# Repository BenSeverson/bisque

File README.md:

<p align="center">
  <picture>
    <source media="(prefers-color-scheme: dark)" srcset="docs/logo-banner-dark.svg" />
    
  </picture>
</p>

<p align="center">

</p>

<p align="center">
  <a href="https://benseverson.github.io/bisque/"><b>▶ Try the live web UI demo</b></a> — interactive, no hardware required
</p>

## Features

**Temperature Control**
- PID controller with auto-tuning (Ziegler-Nichols relay method)
- 1-second control loop with time-proportional SSR output
- Thermocouple calibration offset

**Firing Profiles**
- Up to 20 custom profiles with 16 segments each (ramp rate, target temp, hold time)
- Orton cone firing (cones 022-13) with slow, medium, and fast heating speeds
- Delayed start

**Safety**
- Over-temperature protection (hardware max 1400 C, user-configurable limit)
- Thermocouple fault detection (open circuit, short to GND/VCC)
- Rate-of-rise monitoring (detects runaway >2x programmed rate)
- Not-rising detection (alerts if <10 C rise in 15 min)
- Emergency stop with immediate SSR cutoff

**Web Dashboard**
- Real-time temperature chart with profile overlay (React + Recharts)
- Profile builder with cone fire mode
- Firing history with CSV trace export and cost estimation
- Settings: calibration, safety limits, webhooks, API token

**iOS App**
- Full remote control (SwiftUI)
- Finds the kiln on your Wi-Fi automatically (Bonjour), no IP address to type
- Dynamic Island live activities during firing
- Local notifications for firing complete/error

**LCD Display**
- 4.0" TFT (480x320) with LVGL, adaptive single-screen dashboard (idle/active/paused/complete/error)
- 5-way nav switch (up/down/select/left/right), SELECT-driven modals for profile pick and firing control

**Connectivity**
- Wi-Fi with mDNS (`bisque.local`)
- REST API with optional bearer token auth
- WebSocket for real-time streaming
- Webhook notifications (firing complete/error)

## Screenshots

**Web Dashboard** (React)

**LCD Display** (LVGL on 4.0" TFT)

**iOS App** (SwiftUI)

## Hardware

The controller is a single board in [`hardware/kicad/`](hardware/kicad/) — a full KiCad project (schematic + routed **4-layer** board, 100 × 100 mm). Its GPIO map is [`docs/pin-assignments.md`](docs/pin-assignments.md).

It integrates the ESP32-S3-WROOM-1U module (external U.FL antenna), two MAX31856 thermocouple front-ends, two SSR drive channels behind a hardware watchdog, an ADE7953 current-sense front-end, a ULN2003 auxiliary output bank, three protected dry-contact inputs, USB-C flashing, status LED, and alarm buzzer — with screw terminals for the field wiring and keyed connectors for the display and nav-switch looms. Gerbers, drill files, and an assembly BOM/CPL are committed and ready to upload to a board house.

See [`hardware/kicad/README.md`](hardware/kicad/README.md) for the full BOM, fabrication notes, and the regeneration workflow. GPIO assignments mirror the firmware's `Kconfig` defaults, so stock firmware runs unmodified.

[`hardware/enclosure/`](hardware/enclosure/README.md) documents a complete enclosure build around an off-the-shelf wall-mount steel box — layout, SSR thermal sizing, mains/SELV segregation, and a printable 1:1 drill template for the door.

> **Safety warning:** Kilns operate at dangerous temperatures and voltages. Ensure all high-voltage wiring is performed by a qualified electrician. Use appropriate safety equipment and never leave a firing kiln unattended.

## Getting Started

### Prerequisites

- [ESP-IDF v6.1](https://docs.espressif.com/projects/esp-idf/en/v6.1/esp32s3/get-started/)
- Node.js 18+
- [XcodeGen](https://github.com/yonaskolb/XcodeGen) (for iOS development)

### Dev Container (recommended)

The fastest way to a reproducible toolchain is the VS Code dev container — it
pins the exact ESP-IDF v6.1 image CI uses plus Node 24, the static-analysis
tools, and the Claude Code CLI. Open the repo in VS Code and run **Dev
Containers: Reopen in Container**. Everything below (firmware build, web UI,
`make ci`) then works in the container terminal; only flashing needs a bench.
See [docs/devcontainer.md](docs/devcontainer.md).

### Firmware

```bash
# Build web UI assets first
cd web_ui && npm install && npm run build && cd ..

# Gzip assets for SPIFFS
gzip -k -9 spiffs_data/www/assets/*.js spiffs_data/www/assets/*.css

# Build and flash firmware
source ~/.espressif/v6.1/esp-idf/export.sh
idf.py build
idf.py flash monitor
```

### Web UI Development

```bash
cd web_ui
npm install
npm run dev    # Starts dev server with mock kiln simulator
```

### iOS App

```bash
# Generate Xcode project
cd ios/Bisque
xcodegen generate
open Bisque.xcodeproj
```

For simulator testing, start the mock server first:

```bash
cd web_ui && npm run mock-server   # HTTP + WebSocket on localhost:8080
```

In the iOS simulator, tap "Use Mock Server" on the connection screen.

<details>
<summary><strong>Simulator / Mock Server</strong></summary>

A mock kiln server simulates the full API (status, profiles, firing, settings, history, autotune, diagnostics) with realistic temperature physics so you can develop and test without hardware.

### Web UI development

The mock server runs automatically as a Vite plugin when you start the web UI dev server:

```bash
cd web_ui
npm run dev
```

The mock is enabled by default. To disable it and proxy to a real kiln instead:

```bash
VITE_MOCK=false npm run dev
```

Control simulation speed with `VITE_MOCK_SPEED` (default `60` = 60x real-time):

```bash
VITE_MOCK_SPEED=120 npm run dev
```

### iOS app development

A standalone mock server is available for testing the iOS app in the Xcode simulator:

```bash
cd web_ui
npm run mock-server
```

This starts an HTTP + WebSocket server on `localhost:8080`. To change the port or simulation speed:

```bash
MOCK_PORT=9000 MOCK_SPEED=120 npm run mock-server
```

### LCD Simulator

A standalone SDL2-based simulator renders the LVGL display UI on your desktop:

```bash
cd simulator
cmake -B build && cmake --build build
./build/bisque_sim
```

Requires SDL2 (`brew install sdl2` on macOS).

</details>

## Architecture

```
main/                 App entry point, FreeRTOS task creation
components/
  app_config/         Pin definitions, hardware constants
  thermocouple/       MAX31856 SPI driver (2 channels)
  pid_control/        PID controller + Ziegler-Nichols auto-tune
  firing_engine/      Multi-segment firing state machine
  safety/             Watchdog, over-temp, fault detection
  cone_table/         Orton cone temperature lookup (022-13)
  history/            Firing history + temperature traces (NVS)
  display/            ST7796S LCD + LVGL UI (adaptive dashboard)
  web_server/         REST API + WebSocket server
  wifi_manager/       Wi-Fi STA/AP + mDNS
web_ui/               React/TypeScript web dashboard
ios/Bisque/           SwiftUI iOS app
simulator/            LVGL SDL2 desktop simulator
tests/host/           Pure-logic + accelerated firing unit tests (CMake/Unity)
docs/                 Wiring diagrams, screenshots, bench smoke test
```

## Testing

CI runs five automated test layers on every PR — pure-logic unit tests
and accelerated firing scenarios (`tests/host/`), a UI screenshot
regression suite (`simulator/ --diff`), web UI unit tests, and a
cross-language API contract test that validates firmware JSON output
against the frontend's zod schemas.

Before tagging a release, run the [bench smoke test](docs/bench-smoke-test.md) — a 3-8 minute hardware
run that verifies the parts CI can't touch: real SSR clicks, real
thermocouple readings, history persistence across reboot.

## Network security

**Bisque assumes the network it sits on is trusted.** It is a LAN-only
device: the HTTP API and the WebSocket telemetry feed are plain `http://`
and `ws://`, with no TLS. Anyone who can see traffic on the same Wi-Fi can
read the API token and every command sent with it.

The optional API token (Settings → API Token) is therefore a lock on the
front door, not protection against a hostile network. It stops a
housemate's laptop or a curious guest from starting a firing; it does not
stop someone who is already capturing your Wi-Fi traffic. Concretely:

- The token is sent as an `Authorization: Bearer` header on every REST
  request and compared in constant time on the device.
- The WebSocket telemetry feed (`/api/v1/ws`) is authenticated by the same
  check as the REST API. Browsers cannot set headers on a WebSocket
  handshake, so the web UI presents the token as a `?token=` query
  parameter instead — which means that on this one route the credential does
  reach anywhere the URL does, including proxy logs and browser history. The
  iOS app uses `URLSession`, which can set the header, and does. Dropping the
  query parameter would lock every browser out of live telemetry, so it is a
  deliberate trade rather than an oversight.
- Firmware updates are fetched over HTTPS with certificate validation
  against the bundled root store, and the downloaded image is checked
  against the SHA-256 in the release manifest. So an OTA is not exposed by
  the local network being readable — its trust rests on GitHub's TLS, not on
  your LAN.

If that trust assumption does not hold for your network, put the kiln on an
isolated VLAN or guest SSID rather than relying on the token. TLS on-device
with certificate pinning in the clients has been considered and is tracked
in [#149](https://github.com/BenSeverson/bisque/issues/149); it is a
significant amount of firmware and app complexity for a home LAN, and has
not been implemented.

**Never expose a kiln controller directly to the internet.** No port
forwarding, no DMZ. This is a device that applies mains power to a heating
element in an unattended room.

## Releases

Firmware is distributed as [GitHub Releases](https://github.com/BenSeverson/bisque/releases),
each with a full ESP32-S3 flash kit and Sigstore build-provenance
attestations. See [RELEASING.md](RELEASING.md) for the versioning scheme and
the procedure for cutting a release.

## License

[MIT](LICENSE)

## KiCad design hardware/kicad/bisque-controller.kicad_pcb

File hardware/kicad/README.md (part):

# Bisque Kiln Controller — KiCad PCB

The controller board. This is **rev B**, a respin of the original prototype
rather than a variant — it replaced the thermocouple front-end with an
incompatible part, added a second SSR zone and a digital current-sense chip,
moved most GPIOs, and swapped the module variant.
4-layer, 100 × 100 mm, built for **JLCPCB assembly**: 0805 passives,
QFN/TSSOP/SOIC/SOT ICs, SMD tact switches and the ESP32-S3-WROOM-1U module's
castellated pads all go down the SMT line, and JLCPCB hand-solders the twelve
through-hole parts (terminals, wafers, buzzer) on the same order — see
"Fabrication & assembly" below for why that is cheaper than fitting them
yourself. The design record for
this respin, including the routing escalation that forced the layer count,
is `docs/superpowers/specs/2026-08-10-pcb-rev-b-hardware-design.md`; the
fab-readiness sign-off is `FAB-READINESS-REVIEW-REVB.md`.

Built and validated with **real KiCad** (10.0.5, pcbnew Python API +
kicad-cli): footprints come from KiCad's installed libraries, ground/power
plane pours are filled and checked by `kicad-cli pcb drc --refill-zones` —
**zero errors, zero unconnected, zero warnings**
(`bisque-controller-drc.rpt`) — and the schematic passes a netlist round-trip
check (KiCad's exported netlist diffed against the design's connectivity
table — 92 nets, 0 mismatches). The 3D renders in `3d/` are raytraced by
`kicad-cli pcb render` with the official component models.

| File | What it is |
|---|---|
| `bisque-controller.kicad_pro` | Project. Hand-maintained **except** two blocks, both derived and both written *after* the board is saved because `pcbnew.SaveBoard()` blanks them: `schematic.top_level_sheets` (`project_sync.py::sync_project()`) and `net_settings` (`gen_pcb.py::sync_netclasses()`, from `ROUTE_ORDER`) — see below |
| `bisque-controller.kicad_sch` | Root of the hierarchical schematic: a sheet symbol per functional area (`sheets/power`, `mcu`, `kiln`, `io`, `ct`) plus the notes block and the mechanical parts (mounting holes H1–H4, fiducials FID1–FID3), wired as a block diagram: each sheet symbol carries a pin per net that crosses sheets. Within a sheet: one hierarchical label per crossing net, local labels for everything else, real power ports for rails; no global labels. Hand-owned; `make pcb-netlist` exports its connectivity. |
| `bisque-controller.kicad_pcb` | Board: placed, fully routed, 4 layers (F.Cu/B.Cu signals, In1.Cu GND plane, In2.Cu +3V3 plane), on JLCPCB's `JLC04161H-7628` 1.6 mm stack-up — see "The physical stack-up" |
| `bisque-controller.kicad_dru` | JLCPCB's standard 4-layer process as KiCad custom rules — **not generated**, and not a statement of design intent: every limit in it is JLC's *absolute minimum*, so a violation means something slipped off the design's own floor (0.3 mm track, 0.2 mm clearance, 0.6/0.3 vias, all from `net_settings`) far enough to hit the fab's. KiCad reads it by project name, so it survives regeneration untouched and the existing `kicad-cli pcb drc` pass picks it up for free — see "Fabrication & assembly at JLCPCB" |
| `3d/board-3d-*.png` | Raytraced renders, kicad-cli — straight orthographic **top** and **bottom** only. The angled iso/front views were dropped: they look better than they read, and these images get used to check placement and silk, not to advertise |
| `bisque-controller-drc.rpt` | KiCad DRC report, now including the `.kicad_dru` rules above (0 errors, 0 unconnected, 0 warnings — the 109 silkscreen warnings went with the silk packer, see "Regenerating the files") |
| `gerbers/` | Fabrication outputs (kicad-cli: F.Cu, B.Cu, **In1.Cu, In2.Cu**, paste/silk/mask, Edge.Cuts, Excellon drill + job file) |
| `pdf/` | Schematic and board PDFs (kicad-cli) |
| `jlcpcb/` | The complete JLCPCB upload: `gerbers.zip` for fabrication, BOM + CPL for assembly, plus the shopping list for the parts you could hand-solder instead, and `mouser-order.csv` for the mating connectors |
| `generator/` | Scripts that build everything from one connectivity table |

## Opening it

Open `bisque-controller.kicad_pro` in KiCad 10 or newer (the board file
format and pcbnew API this generator uses require it — see "Regenerating the
files"). Zones ship **filled** (KiCad's own filler) and the board already
passes KiCad DRC; re-run it after any edit. The schematic embeds its
symbols; the board references the standard KiCad footprint libraries (and
was generated from them), plus the four vendored models in `3dmodels/`.

**Opening the project used to dirty it.** KiCad records the root sheet under
`schematic.top_level_sheets` in the `.kicad_pro` and writes that block itself
the first time anything touches the project — and what it writes depends on
who wrote it. The GUI knows the schematic's real root uuid; `kicad-cli pcb`
fills all-zeros, because the PCB tooling never loads a schematic and has no
uuid to record. So the file grew an unexplained diff after a regen and could
flip between two values depending on which tool ran last.

`project_sync.py::sync_project()` (used by `sync_board.py`) now derives the entry from the same `ROOT`
constant the schematic's own `(uuid ...)` comes from, and runs on every
`pcb-sync`. Whoever opens the project next finds it already
correct and leaves it alone — kicad-cli only ever *adds* the block when it is
missing and preserves a populated one, which is what makes deriving it
sufficient rather than a tug-of-war. The rewrite is a whole-file json
round-trip, safe because KiCad emits plain 2-space-indented JSON that
re-dumps byte for byte; do not replace it with a hand-rolled text patch.

## What's on the board

- **U1 — ESP32-S3-WROOM-1U-N16R2** module (16 MB flash / 2 MB **quad**
  PSRAM — matches `sdkconfig.defaults`' `CONFIG_SPIRAM_MODE_QUAD` + the
  16 MB OTA partition table), at the top edge. The **1U** variant carries a
  **U.FL connector for an external antenna** rather than the standard
  WROOM-1's on-package PCB antenna: a kiln controller mounts on or near a
  large grounded steel enclosure, which makes a PCB antenna close to
  non-functional, and the 1U's antenna can be placed on a pigtail somewhere
  that actually radiates. It also reclaims the ~330 mm² antenna keep-out
  band the WROOM-1 footprint would require — freed for parts and ground
  pour on a board that turned out to need every square millimeter (see
  "Density and the 4-layer stack-up" below). **The U.FL pigtail (U.FL → SMA
  bulkhead) and the 2.4 GHz antenna are accessories, not BOM lines** — buy
  them separately (see the hand-solder/shopping-list note below) and drill
  an SMA bulkhead hole in the enclosure. U.FL is rated for ~30 mating
  cycles, so treat the connection as assemble-once, not a field-serviceable
  connector.

  **Certification caveat.** Espressif's modular certification for the
  WROOM-1U is granted against specific antenna types and gains. Fitting a
  non-approved (e.g. high-gain) antenna steps outside that approval — see
  `CERT-001` in `FAB-READINESS-REVIEW-REVB.md`. Use an antenna within the
  certified list unless you're prepared to re-certify.

- **Power**: 24 V DC in on screw terminal **J2** (top-left) *or* USB-C.
  The 24 V side runs J2 → F1 (750 mA/33 V resettable fuse) → D8 (SMAJ30A TVS)
  → **Q8** (AO3401A P-FET, reverse polarity) → **U11**, an XL1509-5.0 buck in
  the south-east corner that makes `BUCK_5V`; **U12** (TPS2116) then selects
  between `BUCK_5V` and USB VBUS to make `+5V`, and a **TLV1117LV33**
  (U2, SOT-223) drops that to 3V3.
  Regulating rather than dropping is the point: +5V used to be literally the
  input minus a Schottky, so every diode drop and every turn of the
  installer's trim pot landed on the WS2812B threshold, the SSR drive and the
  relay coil at once. Both of the board's remaining series diodes are now
  gone with it — the reverse-polarity SS34 is Q8 (~39 mV instead of ~0.4 V,
  which matters because `VIN_P` feeds both 24 V SSR terminals as well as the
  buck) and the USB ORing SS34 is U12 (~40 mΩ).

  **U12 runs in priority mode, not highest-voltage-wins, and that is the
  whole reason it is a mux and not an ideal diode.** A 5.25 V USB host is
  higher than a 5.0 V buck, so a plain ORing part would let a laptop source
  the relay bank and both SSR terminals; the diode used to prevent that for
  free by dropping. MODE ties to VIN1 and R63/R64 divide `BUCK_5V` into PR1
  with a 4.0 V threshold, so the buck wins whenever it is up. U12 also
  blocks USB back-feeding the unpowered buck, which closes fab-review
  finding **C1** (5 V on U11's FB and switch pins during every USB-only
  flashing session). Its ST pin is left unconnected on purpose — see
  `DESIGN-NOTES.md` at U12 for why that GPIO is not worth the route.

  `BUCK_5V` and `+5V` are deliberately separate nets: C44/**C46** are the
  buck's compensation (C46 is the electrolytic supplying the ESR zero — since
  2026-10-28 a Panasonic FK with its 0.36 Ω *specified* at 100 kHz, beside one
  22 µF ceramic rather than two; `DESIGN-NOTES.md` at C46 and C44) and
  belong on the buck's side of the mux, not the load's. The input pair C41/C42
  is chosen on Samsung's bias curve: 1210 X7R 4.7 µF holding 3.1 µF each at
  24 V, where the 1206 10 µF they replace held 1.35 µF. The 5 V rail is rated
  1.0 A at 50 °C in-box ambient (`DESIGN-NOTES.md` at C41, "LOAD BUDGET");
  the regulator's 2 A headline is not a rating of this board.
  Power LED (green) on 3V3. The display (below) draws from +5V directly, not
  through U2 — its backlight and panel logic were the dominant unmodeled load
  on the LDO, and moving them off keeps U2's junction temperature comfortably
  under its 125°C limit even at a hot enclosure ambient. The +3V3 rail also
  now lives on its own **inner plane** (In2.Cu) rather than a surface pour —
  see the stack-up note below.
- **Thermocouples ×2**: **MAX31856MUD+** (U3 channel 1 / U5 channel 2,
  TSSOP-14), K-type on screw terminals **J3** (channel 1) / **J8** (channel
  2), each with its datasheet-specified differential + common-mode input
  filter, sharing the SPI bus (MISO + its own CS: `TC1_CS` / `TC2_CS`). This
  replaces rev A's single MAX31855KASA+ entirely — the two parts are not
  pin-compatible, and no attempt was made to support both on one board.

  **Ungrounded-junction thermocouple probes are required.** Both MAX31856s
  reference their T− input to board ground. Two grounded-junction probes
  sharing one kiln chamber would form a ground loop through the kiln body
  itself; use ungrounded-junction (isolated-tip) K-type probes on both
  channels. This is a documentation obligation, not something the board
  enforces electrically.
- **SSR drive ×2, 24 V opto-driven high-side P-FET, ground-referenced (rev
  B.4)**: screw terminals **J4** (zone 1) / **J9** (zone 2), each
  **pin 1 = the switched +** (`SSR1_OUT` / `SSR2_OUT`, silk `OUT`) and
  **pin 2 = board `GND`**. Per channel: GPIO → 220 Ω → the LED of a TLP291
  (**U8** zone 1, **U9** zone 2) → GND; the opto's transistor pulls the gate
  of an **LP2309LT1G** (**Q5** / **Q6**, 60 V P-channel) down through
  **10 kΩ** (R69/R70), an **8.2 V zener** (D13/D14) gate-to-source sets the
  drive from the rail, and **10 kΩ** (R7/R20) gate-to-source holds it off.
  Both sources hang off **`SSR_24V`**, which is `VIN_P` through **Q9**, a
  third LP2309LT1G that is the watchdog's cutoff (see below). A green
  indicator LED (LED3/LED4, amber before the 2026-11-07 BOM-line merge) + 10 kΩ sits across each terminal pair, so it lights only
  when the channel is actually conducting. **D9**/**D10** freewheel each
  terminal for inductive loads. The board supplies the SSR control loop.
  (The SSRs themselves and all mains wiring stay outside this board.)
  Because the `−` pin is ground, an SSR lead that chafes onto the earthed
  enclosure is the wiring diagram, not a fault — the 2026-10-05 review's
  item 3, which B.2's switched-return topology could not cover. Rev B.2/B.3
  boards had pin 1 always live (silk `24V`) and switched the return; the
  pin order is unchanged, so a loom built to that silk still lands right.

  **Current budget, and it is a limit rather than a note.** The two channels
  share what is left of F1's *derated* hold current after the buck: **280 mA
  at the board's 50 °C in-box rating, 180 mA at 60 °C** (derived at F1 in
  `DESIGN-NOTES.md`, 2026-10-29, from the PPTC's derating table, the
  HDR-15-24's own derating and U11 at its 1.0 A ceiling). Two SSR inputs
  plus their indicators is ~40 mA and fits at any ambient. One 24 V coil
  beside an SSR: ≤ 260 mA (6.2 W) at 50 °C, ≤ 160 mA at 60 °C — a 5.4 W
  TeSys-D-class coil fits at 50 °C and not at 60. Two coils: ≤ 140 mA each
  at 50 °C, ≤ 90 mA each at 60 °C. The "~400 mA" quoted before was the 25 °C
  figure. F1 is not enlarged to buy more: under the in-box supply the
  supply's 0.63 A is the next limit anyway, and a 1.1 A PPTC's 2.2 A trip
  would put the clamped fault rail at 39.9 V against U11's 40 V.

  **The optocouplers are containment, not isolation, and that distinction is
  load-bearing.** Rev B opto-*isolated* both channels — dry-contact terminals,
  a four-layer pour keepout across the opto row, `SJ3`/`SJ4` to tie each
  collector to board +5 V, and `check_isolation.py` — and that was **reversed**
  before fab, because an optocoupler only isolates if the SSR control loop is
  powered from a supply that is *not this board*, and this board's is.
  **That reasoning still stands and is not being overturned.** These terminals
  are still board-powered, both sides still share `GND`, and there is still no
  pour keepout, no router keepout, no rule area and no `check_isolation.py`.
  Do not re-add any of them; read commit `93a31d7` first.

  What changed is the failure the parts are bought for. At 5 V, a channel
  MOSFET failing gate-to-drain put 5 V through 100 Ω into a GPIO and the
  ESP32's clamp survived it. At 24 V the same single failure puts ~240 mA into
  that clamp and takes the module with it. The opto removes the conductor: the
  only thing the MCU touches is an LED. It is also not more parts than the
  alternative — a gate-to-GND zener contains the same fault for the same one
  part per channel, but contains it *by conducting*, so it has to survive the
  fault to work and fails open silently.

  **The opto is a TLP291 in SOP-4, not the LTV-817S this started as, and the
  reason is geometry.** The SMD-DIP4 body is 12.04 mm across its courtyard;
  the corridor between `J4`/`J9` and the rest of the block is ~5.5 mm and has
  to carry both these parts and the four per-terminal legends (`OUT`/`GND`,
  each locked to its own screw's y and free only in x). A 12 mm opto leaves
  those legends nowhere to go, and they print on the terminal body — three
  `check_silk` failures that no amount of re-spacing fixes, because the
  corridor is simply too narrow. At 8.50 × 3.10 mm it opens to ~6.7 mm.
  It costs one Extended feeder where the LTV-817S was Basic, and buys 80 V
  `V_CEO` against 35 V, which is free margin on a 24 V board.

  The 220 Ω is sized against the ESP32's **guaranteed** `V_OH`
  (0.8 × VDD = 2.64 V), not against 3.3 V: the opto's CTR bin is only
  specified at `I_F` = 5 mA and falls off steeply below it, and 330 Ω at that
  corner gives 4.7 mA. 220 Ω gives 7.0 mA there, 5.6 mA with `V_F` also at
  its maximum, and 10.0 mA typical — half the ESP32's recommended source
  current.

  The gate drive comes from a **zener, not from the opto's CTR**, and that is
  deliberate: with the opto saturated the R69/R7 pair alone would put half
  the rail across the gate (11.9 V at 24 V, 18.8 V in a clamped 38 V fault,
  24 V on the 48 V transient), so D13/D14 clamp `V_SG` to 8.2 V from
  ~17 V upwards — the whole 21.6–29 V trim range and the fault alike. The
  opto then sinks (`V_rail` − 8.5 V)/10 kΩ: 1.55 mA at 24 V, 2.95 mA in the
  fault, against the ≥ 5.6 mA a GB-rank TLP291 passes at the worst-case LED
  current. Off, the opto's 50 µA of 85 °C dark current across R7 is 0.5 V
  against the LP2309LT1G's 1 V minimum threshold. Rev B.2 got the same
  "from a rail, not a ratio" property by hanging the opto collectors on the
  5 V `SSR_EN`; that rail now has nothing to do with the channels directly.

  **Hardware watchdog (`SJ2`, "WDT DEFEAT").** `SSR_EN` — since rev B.2 a
  +5 V **gate-drive** rail rather than the terminal supply — is supplied by
  Q4, a P-channel high-side MOSFET (AO3401A) whose gate node `SSR_PG` is held
  down by Q3, itself held on by **U10**, an SN74LVC1G123 retriggerable
  monostable driven from `WDT_KICK`; R47 (100 kΩ) pulls `SSR_PG` up
  as the fail-safe. `SSR_EN` enhances **Q7** (CJ2310), which pulls the gate
  of **Q9** — the 24 V high-side cutoff between `VIN_P` and `SSR_24V` — down
  through R71 (10 kΩ); D12 clamps Q9's `V_SG` to 8.2 V and **R22** (100 kΩ,
  gate to source) holds Q9 off whenever Q7 is not pulling. When the window
  expires `SSR_EN` falls, R18 (10 kΩ) takes Q7's gate down, R22 takes Q9's
  gate to its source and `SSR_24V` is dead: both terminals are off whatever
  the channel switches are doing, a failed-short channel included. **R18**
  is what makes that work — `SSR_EN` is Q4's *drain*, so with Q4 off nothing
  would define it and Q7's gate would float, the same fail-dangerous bug R49
  exists to fix one node upstream.

  **Q9 is the high-side cutoff B.2 rejected, and the reason it was rejected
  is gone.** B.2 kept the watchdog in the shared *return* (Q7 as the switch)
  because no fee-free 60 V P-channel part existed at JLCPCB; the only one was
  a 50 V/130 mA BSS84 that capped the terminals below their own budget. On
  Standard PCBA — which U1 and C46 force — every line pays the same $1.53,
  and the LP2309LT1G (60 V, 1.9 A, LCSC C383253) is the part the objection
  said did not exist. The return-side watchdog also could not touch an SSR
  `−` lead that found ground (review A1 / item 3), and it let a failed-short
  channel put −23.7 V on the healthy channel's gate through R22 (item 11);
  with the switches on the + side and the cutoff in series with the rail,
  both of those go away. Q7 survives as the level shift because its gate is
  on a 5 V rail where the CJ2310 is specified, the argument B.2 made for it.

  Every **rising edge** on `WDT_KICK` restarts U10's window, so `Q` stays high
  only while firmware keeps kicking; a pin wedged at either level delivers no
  edge and expires the window exactly like a pin that stopped, which is the
  whole point. R46 (1 MΩ) and C38 ∥ C49 (2 × 1 µF X7R) set the window to
  **1.3–3.1 s** worst-case over −40…125 °C (2.0–2.2 s nominal), every term of
  that bound a datasheet or purchase-tolerance figure. Firmware kicks at 5 Hz
  from the existing 100 ms SSR timer, gated on `safety_task`'s heartbeat
  (`components/safety/wdt_kick.h`) — 6.4× margin at the minimum window. R48
  (100 kΩ) holds `B` low whenever the MCU drives nothing, so a floating CMOS
  input cannot self-trigger the one-shot during boot ROM, flashing or reset.

  **This replaced a BAT54S diode charge pump, which did not work.** Solving its
  steady state exactly gives 0.63 V of gate drive at 5 Hz against Q3's 1.45 V
  threshold — and 0.84 V even in the typical corner, below the *typical* 1.0 V
  threshold. A faster kick (≥ 250 Hz) rescues the voltage but not the
  temperature behaviour: Schottky reverse leakage sits in the timing path and
  roughly doubles per 10 °C, so the budget for a transient firmware stall fell
  from 0.31 s at 25 °C to 0.11 s at 60 °C and vanished near 85 °C, next to a
  5 kW heat source. No choice of passives fixes a leak that *is* the timer;
  the fix was to stop building the timer out of one. Off-the-shelf watchdog
  supervisors (TPS3823, STWD100) were evaluated and rejected on output shape:
  they emit a fixed reset *pulse* per timeout, which would leave the heat rail
  energised 75–95 % of the time under dead firmware. They exist to reboot
  MCUs; gating a rail needs a level.

  On power-up, and on any board where nothing kicks `WDT_KICK`, `SSR_EN`
  collapses and **both SSR channels stay off regardless of what the firmware
  commands them to do.** The silkscreened `SJ2` solder jumper shorts `SSR_PG`
  to GND, holding Q4 on and restoring un-gated behaviour for bring-up and for
  any build without the firmware kick. **A board with neither `SJ2` fitted nor
  a working kick will not heat** — this is the single most likely rev B
  bring-up surprise, more likely to be mistaken for a bad SSR or a
  lid-interlock problem than correctly diagnosed as "nobody is kicking the dog
  yet." `TP12` probes the timing node, which is where a scope settles the real
  window in one measurement. The watchdog gates only the two SSR channels;
  vent, purge, the spare aux channel and the buzzer are unaffected, so a
  stalled controller can still open its vent.
- **Display**: 14-pin Molex KK-254 friction-lock header **J5** for a 4.0"
  ST7796S SPI module (LCDWIKI MSP4021, 480×320, resistive touch) — grown
  from rev A's 8-pin display-only header to carry the panel's full pin set:
  the original 8 signal pins, the panel's `SDO` (pin 9, left unwired in rev
  A because the firmware never read from the display), and the five touch
  lines (pins 10–14). `T_CLK`/`T_DIN`/`T_DO` are electrically the shared
  SPI2 bus through 33 Ω series damping resistors (R39/R41/R42 — the bus now
  multi-drops the LCD at 40 MHz plus two MAX31856s and the touch controller
  at lower clocks); only `T_CS` and `T_IRQ` cost new
  dedicated GPIOs. Since 2026-10-29 (PCB review item 5) SCLK and MOSI also
  leave the ESP32 through **R72/R73** (33 Ω, 0603) ahead of every branch —
  the pin-side stubs are `SPI_SCLK_U1`/`SPI_MOSI_U1` — and four 100 nF
  0603s (**C51–C54**) sit at the bus's layer transitions as +3V3-to-GND
  reference-transfer caps, with 29 GND stitch vias beside the rest (and 31 more, since 2026-10-30, beside the I2C and display/touch transitions). The
  honest coverage figures are in `DESIGN-NOTES.md` §C51; the 40 MHz
  waveforms are a bench check, not a proof. The XPT2046 touch controller itself lives on the display
  module, not this PCB. Since rev B.5 three SRV05-4 arrays (D19–D21) clamp
  all twelve J5 signal lines at the connector, and `LCD_RST`/`LCD_BL`, the
  two that had no series resistor, got 33 Ω (R79/R80). VCC runs from +5V rather than +3V3, per the
  module's own manual and reference wiring diagrams, with no level shifter
  needed on CS/RESET/DC/MOSI/SCK.
- **Nav switch**: 6-pin KK-254 friction-lock header **J6** for the
  panel-mounted 5-way switch (`UP DN LT RT OK GND`, active-low, ESP32
  internal pull-ups) — now on five contiguous module pads, moved from the
  split pins rev A used (routing simplification, see the hardware-design
  spec §3.1). Since rev B.5 an **ESDA6V1-5SC6** five-line array (D18)
  clamps the five switch lines to GND. There is no series resistor on
  them: ten more pad escapes did not fit beside J6 (`DESIGN-NOTES.md`
  §"Connector protection").
- **Aux header J7** (8-pin KK-254): `3V3 GND TX RX SDA SCL 3V3 GND` — UART0
  plus a 0.1" I2C tap (pins 5–8), alongside the Qwiic/STEMMA-QT connector
  **J14**. Rev A's `VENT`/`LID_SW`/`AUX_A`/`AUX_B` nets are gone from this
  header entirely: nothing on the board ever sourced `AUX_A`/`AUX_B` here
  (the real aux outputs are on J10, below), and the lid switch has its own
  terminal (J11). Since rev B.5 the 3V3 pins of J7 and J14 come from
  **U13**, an AP2331SA-7 current-limited switch (0.3–0.5 A short-circuit
  limit), so a shorted peripheral no longer drags the ESP32's rail down,
  and an SRV05-4 (D22) clamps TX, RX, SDA and SCL.
- **Aux output bank — J10 + J15** (two 2-pin terminals, side by side):
  **AUX_VP** (external coil rail) and `AUX1_OUT` (vent) on J10, `AUX2_OUT`
  and `AUX3_OUT` on J15, driven by a shared **ULN2003ADR** Darlington array (U6) with
  integrated freewheel diodes returning to `AUX_VP` — not the board's own
  +5V rail. A gas purge solenoid is realistically 12 V or 24 V DC; the
  ULN2003 is rated 50 V / 500 mA per channel, so `AUX_VP` is meant to be fed
  from an external coil supply. Solder jumper **`SJ1`** (open by default)
  ties `AUX_VP` to board +5V for anyone who only has plain 5V relays. Only
  channel 1 (vent) is driven by firmware today (`safety_update_vent()`);
  channels 2/3 are routed and declared in Kconfig (`KILN_PIN_AUX2`/`AUX3`)
  but undriven.
- **Protected inputs — J11 + J16** (two 2-pin terminals): `IN1`/`IN2` (lid,
  gas flow) on J11, `IN3` (spare) and GND on J16, for dry contacts to GND. Since rev B.5 each channel
  survives a 24 V wire landed on its terminal: a 10 kΩ pull-up to 3V3 and an
  **SMF30CA** bidirectional TVS (D15–D17, 30 V standoff, above the supply's
  29 V trim) sit on the terminal side, and the GPIO sees it through **100 kΩ**
  (R12/R26/R28) with 100 nF to ground, so a miswire puts 0.25 mA into the pin
  and 2.6 mA into the 3V3 rail instead of a short through a rail clamp.
  Firmware leaves the lid pin's internal pull-up off to match
  (`KILN_LID_SWITCH_EXTERNAL_PULLUP`, default on). `IN1` is the
  lid switch and defaults to enabled, matching this board; see
  `docs/pin-assignments.md` §1 for the fail-safe wiring requirement if no
  switch is fitted. `IN2` (gas flow) and `IN3` (spare) are routed but have
  no firmware consumer yet.
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
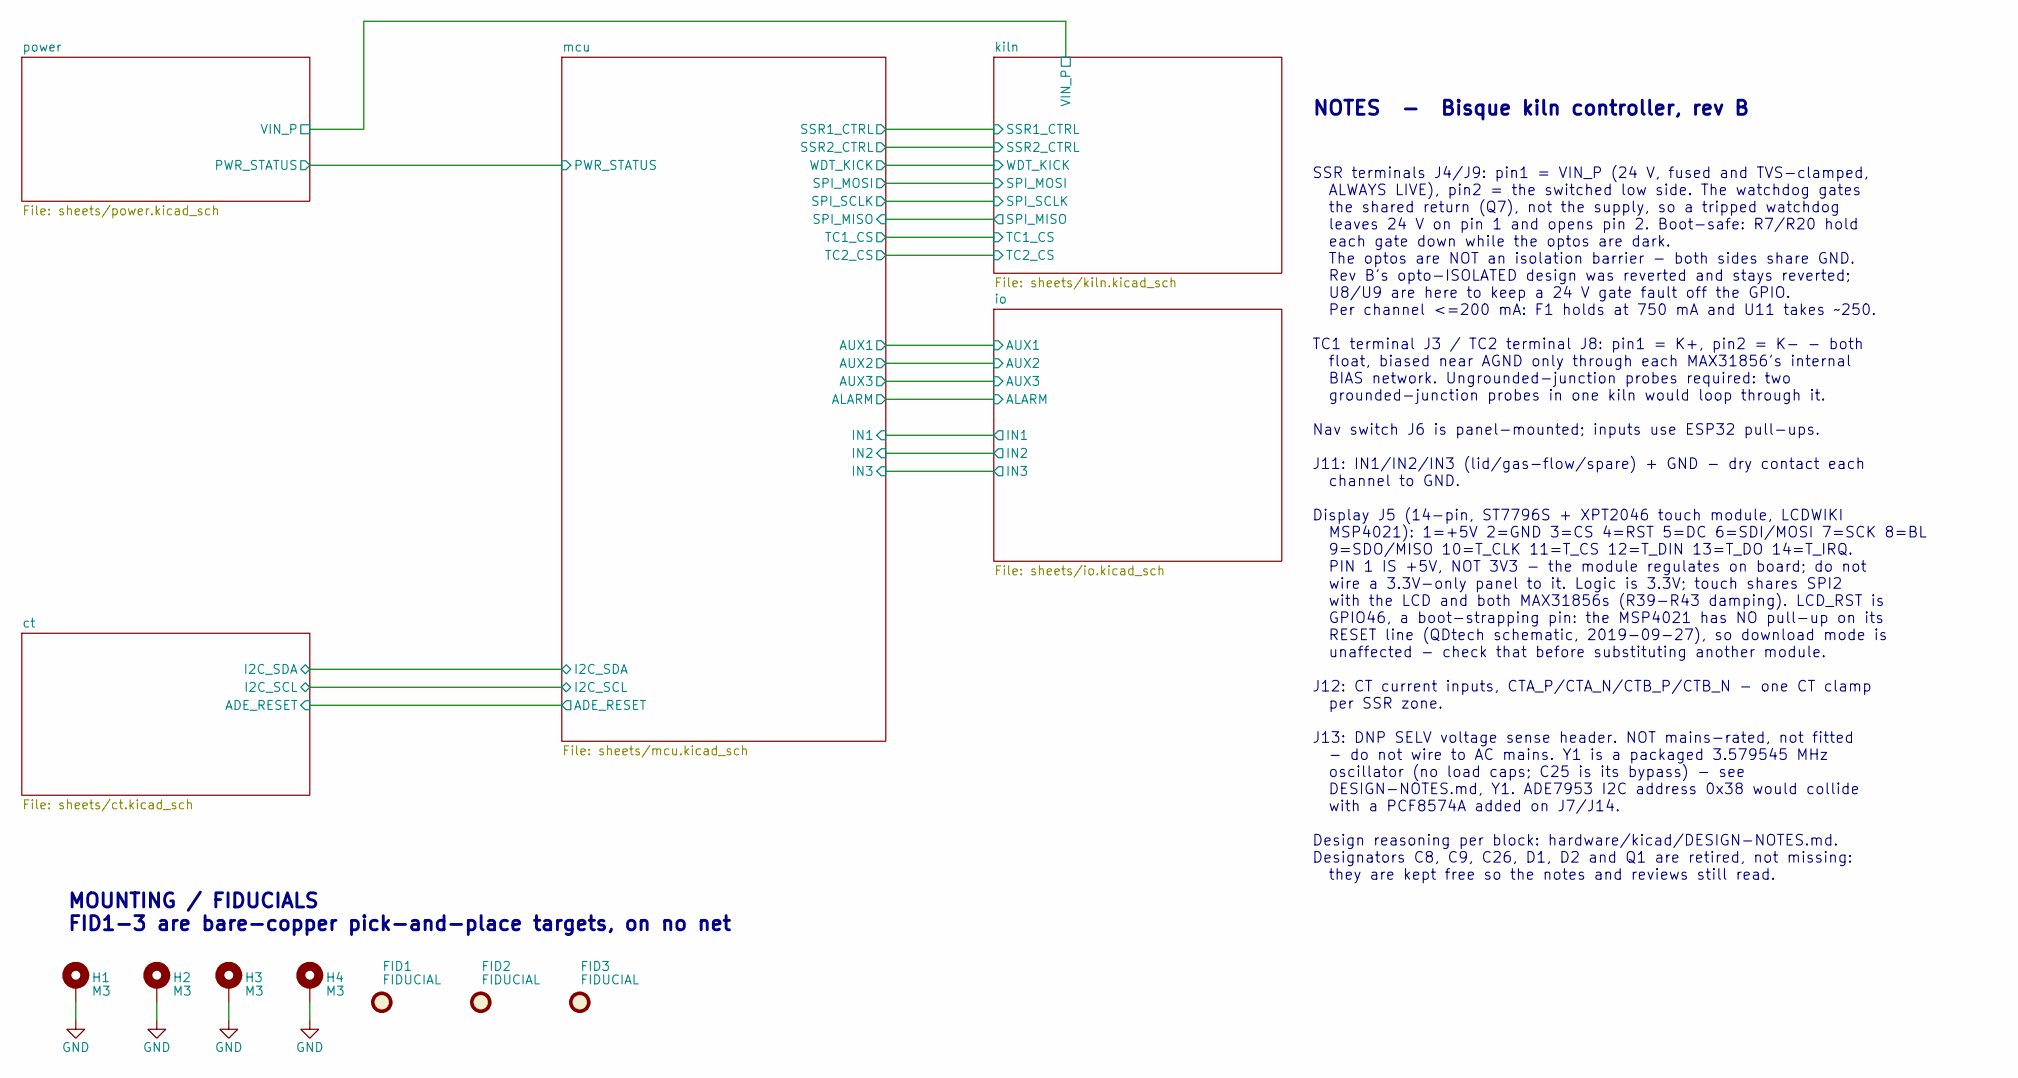
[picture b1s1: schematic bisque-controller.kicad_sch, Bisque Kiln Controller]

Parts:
FID1, FID2, FID3: FIDUCIAL; Fiducial_1mm_Mask2mm
H1, H2, H3, H4: M3; MountingHole_3.2mm_M3_Pad_Via

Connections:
GND: H1.1, H2.1, H3.1, H4.1; also elsewhere on the board

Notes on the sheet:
NOTES - Bisque kiln controller, rev B
SSR terminals J4/J9: pin1 = VIN_P (24 V, fused and TVS-clamped, ALWAYS LIVE), pin2 = the switched low side. The watchdog gates the shared return (Q7), not the supply, so a tripped watchdog leaves 24 V on pin 1 and opens pin 2. Boot-safe: R7/R20 hold each gate down while the optos are dark. The opto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
MOUNTING / FIDUCIALS FID1-3 are bare-copper pick-and-place targets, on no net

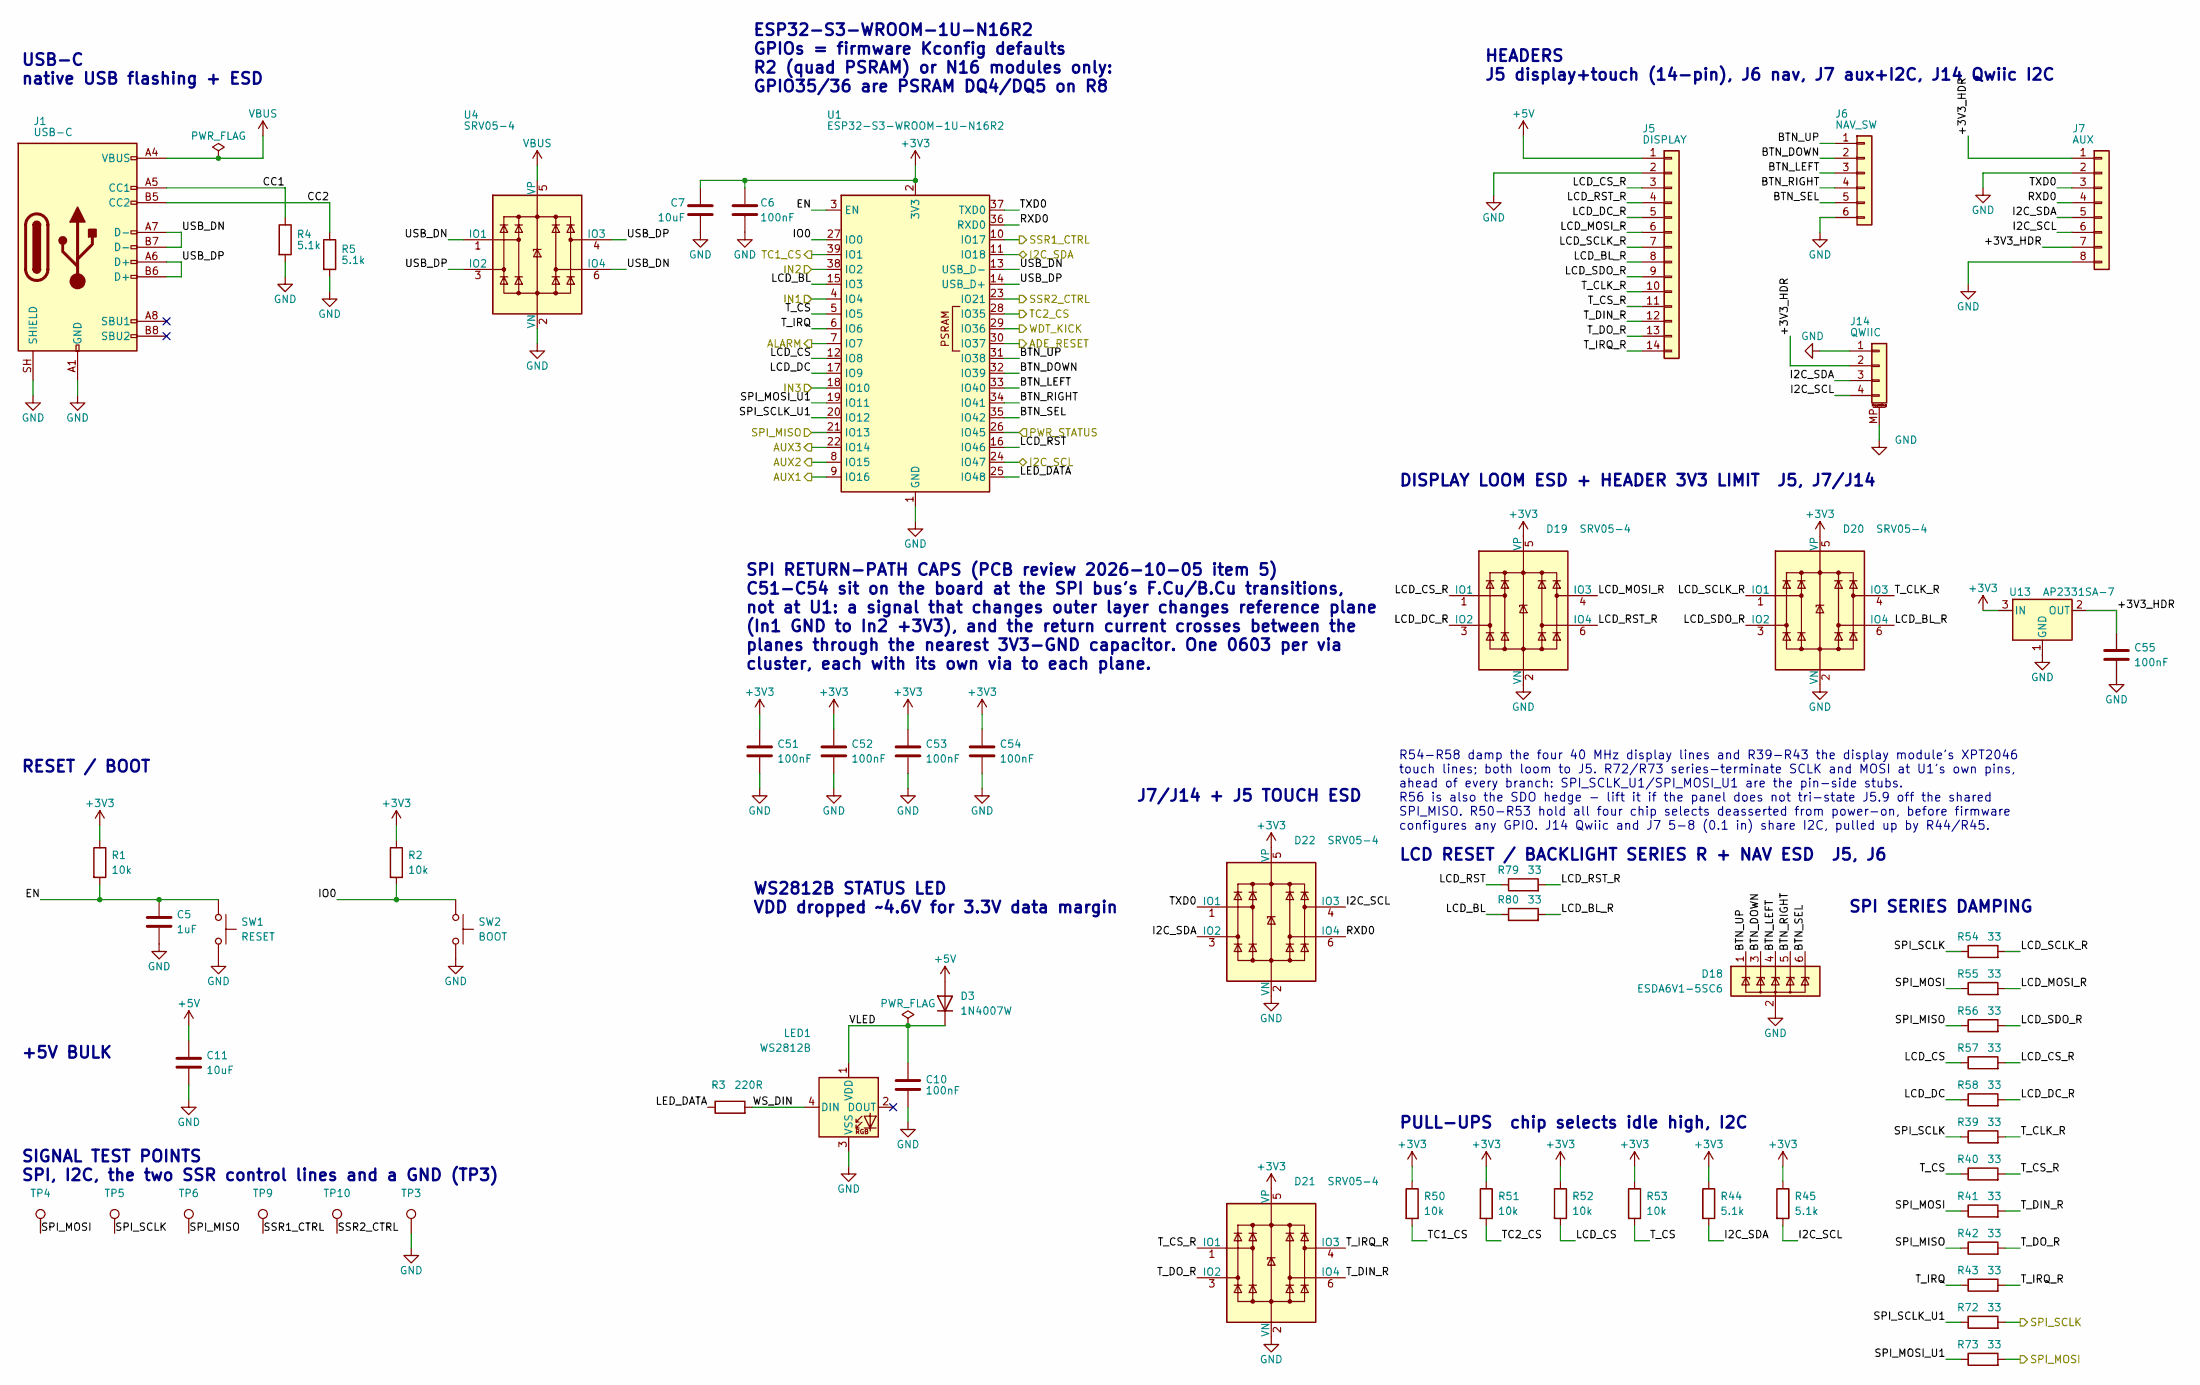
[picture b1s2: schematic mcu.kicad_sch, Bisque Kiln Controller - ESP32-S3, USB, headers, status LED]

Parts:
C5: 1uF; C_0805_2012Metric; MPN CL21B105KBFNNNE; LCSC C28323
C6, C10, C51, C52, C53, C54, C55: 100nF; C_0603_1608Metric; MPN CC0603KRX7R9BB104; LCSC C14663
C7, C11: 10uF; C_0805_2012Metric; MPN CL21A106KAYNNNE; LCSC C15850
D3: 1N4007W; D_SOD-123; MPN 1N4007W; LCSC C3018540
D18: ESDA6V1-5SC6; SOT-23-6; MPN ESDA6V1-5SC6; LCSC C2827672
D19, D20, D21, D22: SRV05-4; SOT-23-6; MPN SRV05-4; LCSC C7420376
J1: USB-C; USB_C_Receptacle_HRO_TYPE-C-31-M-12; MPN TYPE-C-31-M-12; LCSC C165948
J5: DISPLAY; Molex_KK-254_AE-6410-14A_1x14_P2.54mm_Vertical; MPN XD-2510-14A; LCSC C17701004
J6: NAV_SW; Molex_KK-254_AE-6410-06A_1x06_P2.54mm_Vertical; MPN A2547WV-6P; LCSC C239381
J7: AUX; Molex_KK-254_AE-6410-08A_1x08_P2.54mm_Vertical; MPN 22272081; LCSC C240822
J14: QWIIC; JST_SH_SM04B-SRSS-TB_1x04-1MP_P1.00mm_Horizontal; MPN SM04B-SRSS-TB(LF)(SN); LCSC C160404
LED1: WS2812B; LED_WS2812B_PLCC4_5.0x5.0mm_P3.2mm; MPN WS2812E-V5; LCSC C2920042
R1, R2, R50, R51, R52, R53: 10k; R_0805_2012Metric; MPN 0805W8F1002T5E; LCSC C17414
R3: 220R; R_0805_2012Metric; MPN 0805W8F2200T5E; LCSC C17557
R4, R5, R44, R45: 5.1k; R_0805_2012Metric; MPN 0805W8F5101T5E; LCSC C27834
R39, R40, R41, R42, R43, R54, R55, R56, R57, R58, R72, R73, R79, R80: 33; R_0603_1608Metric; MPN 0603WAF330JT5E; LCSC C23140
SW1: RESET; SW_Push_1P1T_XKB_TS-1187A; MPN TS-1187A-B-A-B; LCSC C318884
SW2: BOOT; SW_Push_1P1T_XKB_TS-1187A; MPN TS-1187A-B-A-B; LCSC C318884
TP3: GND; TestPoint_Pad_D1.0mm
TP4: SPI_MOSI; TestPoint_Pad_D1.0mm
TP5: SPI_SCLK; TestPoint_Pad_D1.0mm
TP6: SPI_MISO; TestPoint_Pad_D1.0mm
TP9: SSR1_CTRL; TestPoint_Pad_D1.0mm
TP10: SSR2_CTRL; TestPoint_Pad_D1.0mm
U1: ESP32-S3-WROOM-1U-N16R2; ESP32-S3-WROOM-1U; MPN ESP32-S3-WROOM-1U-N16R2; LCSC C3013945
U4: SRV05-4; SOT-23-6; MPN SRV05-4; LCSC C7420376
U13: AP2331SA-7; SOT-23; MPN AP2331SA-7; LCSC C500764

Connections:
+3V3: C6.1, C7.1, C51.1, C52.1, C53.1, C54.1, D19.5 (VP), D20.5 (VP), D21.5 (VP), D22.5 (VP), R1.1, R2.1, R44.1, R45.1, R50.1, R51.1, R52.1, R53.1, U1.2 (3V3), U13.3 (IN); also elsewhere on the board
+3V3_HDR: C55.1, J7.1, J7.7, J14.2, U13.2 (OUT)
+5V: C11.1, D3.2 (A), J5.1; also elsewhere on the board
ADE_RESET: U1.30 (IO37); also elsewhere on the board
ALARM: U1.7 (IO7); also elsewhere on the board
AUX1: U1.9 (IO16); also elsewhere on the board
AUX2: U1.8 (IO15); also elsewhere on the board
AUX3: U1.22 (IO14); also elsewhere on the board
BTN_DOWN: D18.3 (IO2), J6.2, U1.32 (IO39)
BTN_LEFT: D18.4 (IO3), J6.3, U1.33 (IO40)
BTN_RIGHT: D18.5 (IO4), J6.4, U1.34 (IO41)
BTN_SEL: D18.6 (IO5), J6.5, U1.35 (IO42)
BTN_UP: D18.1 (IO1), J6.1, U1.31 (IO38)
CC1: J1.A5 (CC1), R4.1
CC2: J1.B5 (CC2), R5.1
EN: C5.1, R1.2, SW1.1, U1.3 (EN)
GND: C5.2, C6.2, C7.2, C10.2, C11.2, C51.2, C52.2, C53.2, C54.2, C55.2, D18.2 (GND), D19.2 (VN), D20.2 (VN), D21.2 (VN), D22.2 (VN), J1.A1 (GND), J1.A12 (GND), J1.B1 (GND), J1.B12 (GND), J1.SH (SHIELD), J5.2, J6.6, J7.2, J7.8, J14.1, J14.MP (MountPin), LED1.3 (VSS), R4.2, R5.2, SW1.2, SW2.2, TP3.1, U1.1 (GND), U1.40 (GND), U1.41 (GND), U4.2 (VN), U13.1 (GND); also elsewhere on the board
I2C_SCL: D22.4 (IO3), J7.6, J14.4, R45.2, U1.24 (IO47); also elsewhere on the board
I2C_SDA: D22.3 (IO2), J7.5, J14.3, R44.2, U1.11 (IO18); also elsewhere on the board
IN1: U1.4 (IO4); also elsewhere on the board
IN2: U1.38 (IO2); also elsewhere on the board
IN3: U1.18 (IO10); also elsewhere on the board
IO0: R2.2, SW2.1, U1.27 (IO0)
LCD_BL: R80.1, U1.15 (IO3)
LCD_BL_R: D20.6 (IO4), J5.8, R80.2
LCD_CS: R52.2, R57.1, U1.12 (IO8)
LCD_CS_R: D19.1 (IO1), J5.3, R57.2
LCD_DC: R58.1, U1.17 (IO9)
LCD_DC_R: D19.3 (IO2), J5.5, R58.2
LCD_MOSI_R: D19.4 (IO3), J5.6, R55.2
LCD_RST: R79.1, U1.16 (IO46)
LCD_RST_R: D19.6 (IO4), J5.4, R79.2
LCD_SCLK_R: D20.1 (IO1), J5.7, R54.2
LCD_SDO_R: D20.3 (IO2), J5.9, R56.2
LED_DATA: R3.1, U1.25 (IO48)
PWR_STATUS: U1.26 (IO45); also elsewhere on the board
RXD0: D22.6 (IO4), J7.4, U1.36 (RXD0)
SPI_MISO: R42.1, R56.1, TP6.1, U1.21 (IO13); also elsewhere on the board
SPI_MOSI: R41.1, R55.1, R73.2, TP4.1; also elsewhere on the board
SPI_MOSI_U1: R73.1, U1.19 (IO11)
SPI_SCLK: R39.1, R54.1, R72.2, TP5.1; also elsewhere on the board
SPI_SCLK_U1: R72.1, U1.20 (IO12)
SSR1_CTRL: TP9.1, U1.10 (IO17); also elsewhere on the board
SSR2_CTRL: TP10.1, U1.23 (IO21); also elsewhere on the board
TC1_CS: R50.2, U1.39 (IO1); also elsewhere on the board
TC2_CS: R51.2, U1.28 (IO35); also elsewhere on the board
TXD0: D22.1 (IO1), J7.3, U1.37 (TXD0)
T_CLK_R: D20.4 (IO3), J5.10, R39.2
T_CS: R40.1, R53.2, U1.5 (IO5)
T_CS_R: D21.1 (IO1), J5.11, R40.2
T_DIN_R: D21.6 (IO4), J5.12, R41.2
T_DO_R: D21.3 (IO2), J5.13, R42.2
T_IRQ: R43.1, U1.6 (IO6)
T_IRQ_R: D21.4 (IO3), J5.14, R43.2
USB_DN: J1.A7 (D-), J1.B7 (D-), U1.13 (USB_D-), U4.1 (IO1), U4.6 (IO4)
USB_DP: J1.A6 (D+), J1.B6 (D+), U1.14 (USB_D+), U4.3 (IO2), U4.4 (IO3)
VBUS: J1.A4 (VBUS), J1.A9 (VBUS), J1.B4 (VBUS), J1.B9 (VBUS), U4.5 (VP); also elsewhere on the board
VLED: C10.1, D3.1 (K), LED1.1 (VDD)
WDT_KICK: U1.29 (IO36); also elsewhere on the board
WS_DIN: LED1.4 (DIN), R3.2

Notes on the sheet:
WS2812B STATUS LED VDD dropped ~4.6V for 3.3V data margin
USB-C native USB flashing + ESD
SPI RETURN-PATH CAPS (PCB review 2026-10-05 item 5) C51-C54 sit on the board at the SPI bus's F.Cu/B.Cu transitions, not at U1: a signal that changes outer layer changes reference plane (In1 GND to In2 +3V3), and the return current crosses between the planes through the nearest 3V3-GND capacitor. O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
RESET / BOOT
+5V BULK
R54-R58 damp the four 40 MHz display lines and R39-R43 the display module's XPT2046 touch lines; both loom to J5. R72/R73 series-terminate SCLK and MOSI at U1's own pins, ahead of every branch: SPI_SCLK_U1/SPI_MOSI_U1 are the pin-side stubs. R56 is also the SDO hedge - lift it if the panel does not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
PULL-UPS chip selects idle high, I2C
DISPLAY LOOM ESD + HEADER 3V3 LIMIT J5, J7/J14
J7/J14 + J5 TOUCH ESD
LCD RESET / BACKLIGHT SERIES R + NAV ESD J5, J6
SPI SERIES DAMPING
HEADERS J5 display+touch (14-pin), J6 nav, J7 aux+I2C, J14 Qwiic I2C
SIGNAL TEST POINTS SPI, I2C, the two SSR control lines and a GND (TP3)
ESP32-S3-WROOM-1U-N16R2 GPIOs = firmware Kconfig defaults R2 (quad PSRAM) or N16 modules only: GPIO35/36 are PSRAM DQ4/DQ5 on R8

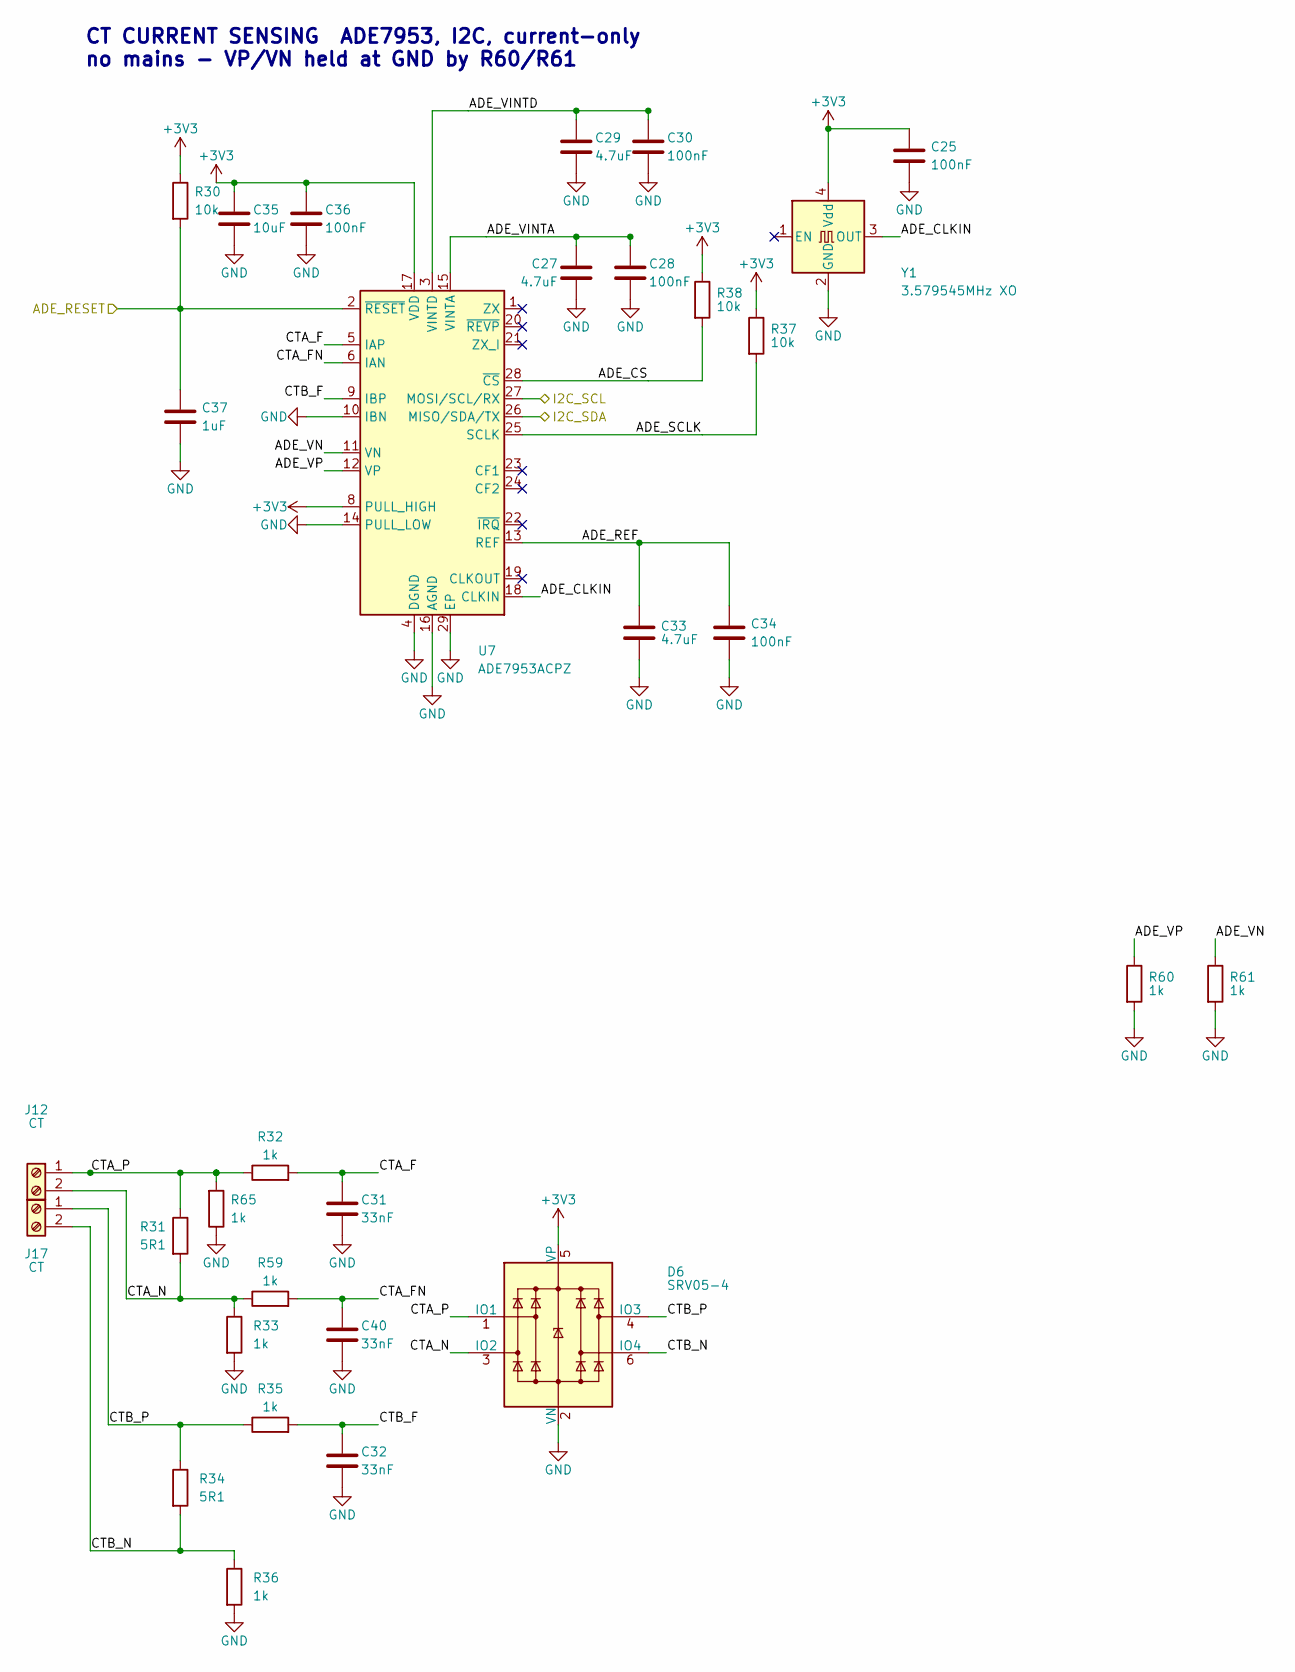
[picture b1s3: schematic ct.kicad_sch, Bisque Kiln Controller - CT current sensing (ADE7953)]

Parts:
C25, C28, C30, C34, C36: 100nF; C_0603_1608Metric; MPN CC0603KRX7R9BB104; LCSC C14663
C27, C29, C33: 4.7uF; C_0805_2012Metric; MPN CL21A475KAQNNNE; LCSC C1779
C31, C32, C40: 33nF; C_0805_2012Metric; MPN 0805B333K500NT; LCSC C1739
C35: 10uF; C_0805_2012Metric; MPN CL21A106KAYNNNE; LCSC C15850
C37: 1uF; C_0805_2012Metric; MPN CL21B105KBFNNNE; LCSC C28323
D6: SRV05-4; SOT-23-6; MPN SRV05-4; LCSC C7420376
J12, J17: CT; TerminalBlock_Phoenix_MKDS-1,5-2-5.08_1x02_P5.08mm_Horizont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; MPN WJ500V-5.08-2P; LCSC C8465
R30, R37, R38: 10k; R_0805_2012Metric; MPN 0805W8F1002T5E; LCSC C17414
R31, R34: 5R1; R_0805_2012Metric; MPN 0805W8F510KT5E; LCSC C17724
R32, R33, R35, R36, R59, R60, R61, R65: 1k; R_0805_2012Metric; MPN 0805W8F1001T5E; LCSC C17513
U7: ADE7953ACPZ; QFN-28-1EP_5x5mm_P0.5mm_EP3.1x3.1mm; MPN ADE7953ACPZ-RL; LCSC C515890
Y1: 3.579545MHz XO; Oscillator_SMD_Abracon_ASE-4Pin_3.2x2.5mm; MPN TFOM3.579545M4RHKCNT2T; LCSC C2838127

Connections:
+3V3: C25.1, C35.1, C36.1, D6.5 (VP), R30.1, R37.1, R38.1, U7.7 (PULL_HIGH), U7.8 (PULL_HIGH), U7.17 (VDD), Y1.4 (Vdd); also elsewhere on the board
ADE_CLKIN: U7.18 (CLKIN), Y1.3 (OUT)
ADE_CS: R38.2, U7.28 (~CS)
ADE_REF: C33.1, C34.1, U7.13 (REF)
ADE_RESET: C37.1, R30.2, U7.2 (~RESET); also elsewhere on the board
ADE_SCLK: R37.2, U7.25 (SCLK)
ADE_VINTA: C27.1, C28.1, U7.15 (VINTA)
ADE_VINTD: C29.1, C30.1, U7.3 (VINTD)
ADE_VN: R61.1, U7.11 (VN)
ADE_VP: R60.1, U7.12 (VP)
CTA_F: C31.1, R32.2, U7.5 (IAP)
CTA_FN: C40.1, R59.2, U7.6 (IAN)
CTA_N: D6.3 (IO2), J12.2, R31.2, R33.1, R59.1
CTA_P: D6.1 (IO1), J12.1, R31.1, R32.1, R65.2
CTB_F: C32.1, R35.2, U7.9 (IBP)
CTB_N: D6.6 (IO4), J17.2, R34.2, R36.1
CTB_P: D6.4 (IO3), J17.1, R34.1, R35.1
GND: C25.2, C27.2, C28.2, C29.2, C30.2, C31.2, C32.2, C33.2, C34.2, C35.2, C36.2, C37.2, C40.2, D6.2 (VN), R33.2, R36.2, R60.2, R61.2, R65.1, U7.4 (DGND), U7.10 (IBN), U7.14 (PULL_LOW), U7.16 (AGND), U7.29 (EP), Y1.2 (GND); also elsewhere on the board
I2C_SCL: U7.27 (MOSI/SCL/RX); also elsewhere on the board
I2C_SDA: U7.26 (MISO/SDA/TX); also elsewhere on the board

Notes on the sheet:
CT CURRENT SENSING ADE7953, I2C, current-only no mains - VP/VN held at GND by R60/R61

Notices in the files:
hardware/kicad/README.md:
**Front:** `BISQUE / KILN CONTROLLER / REV B.5 / © 2026 Ben Severson`, text
